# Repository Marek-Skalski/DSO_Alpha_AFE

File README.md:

# DSO_Alpha_AFE
This repository provides data related to DSO Alpha verision - AFE module

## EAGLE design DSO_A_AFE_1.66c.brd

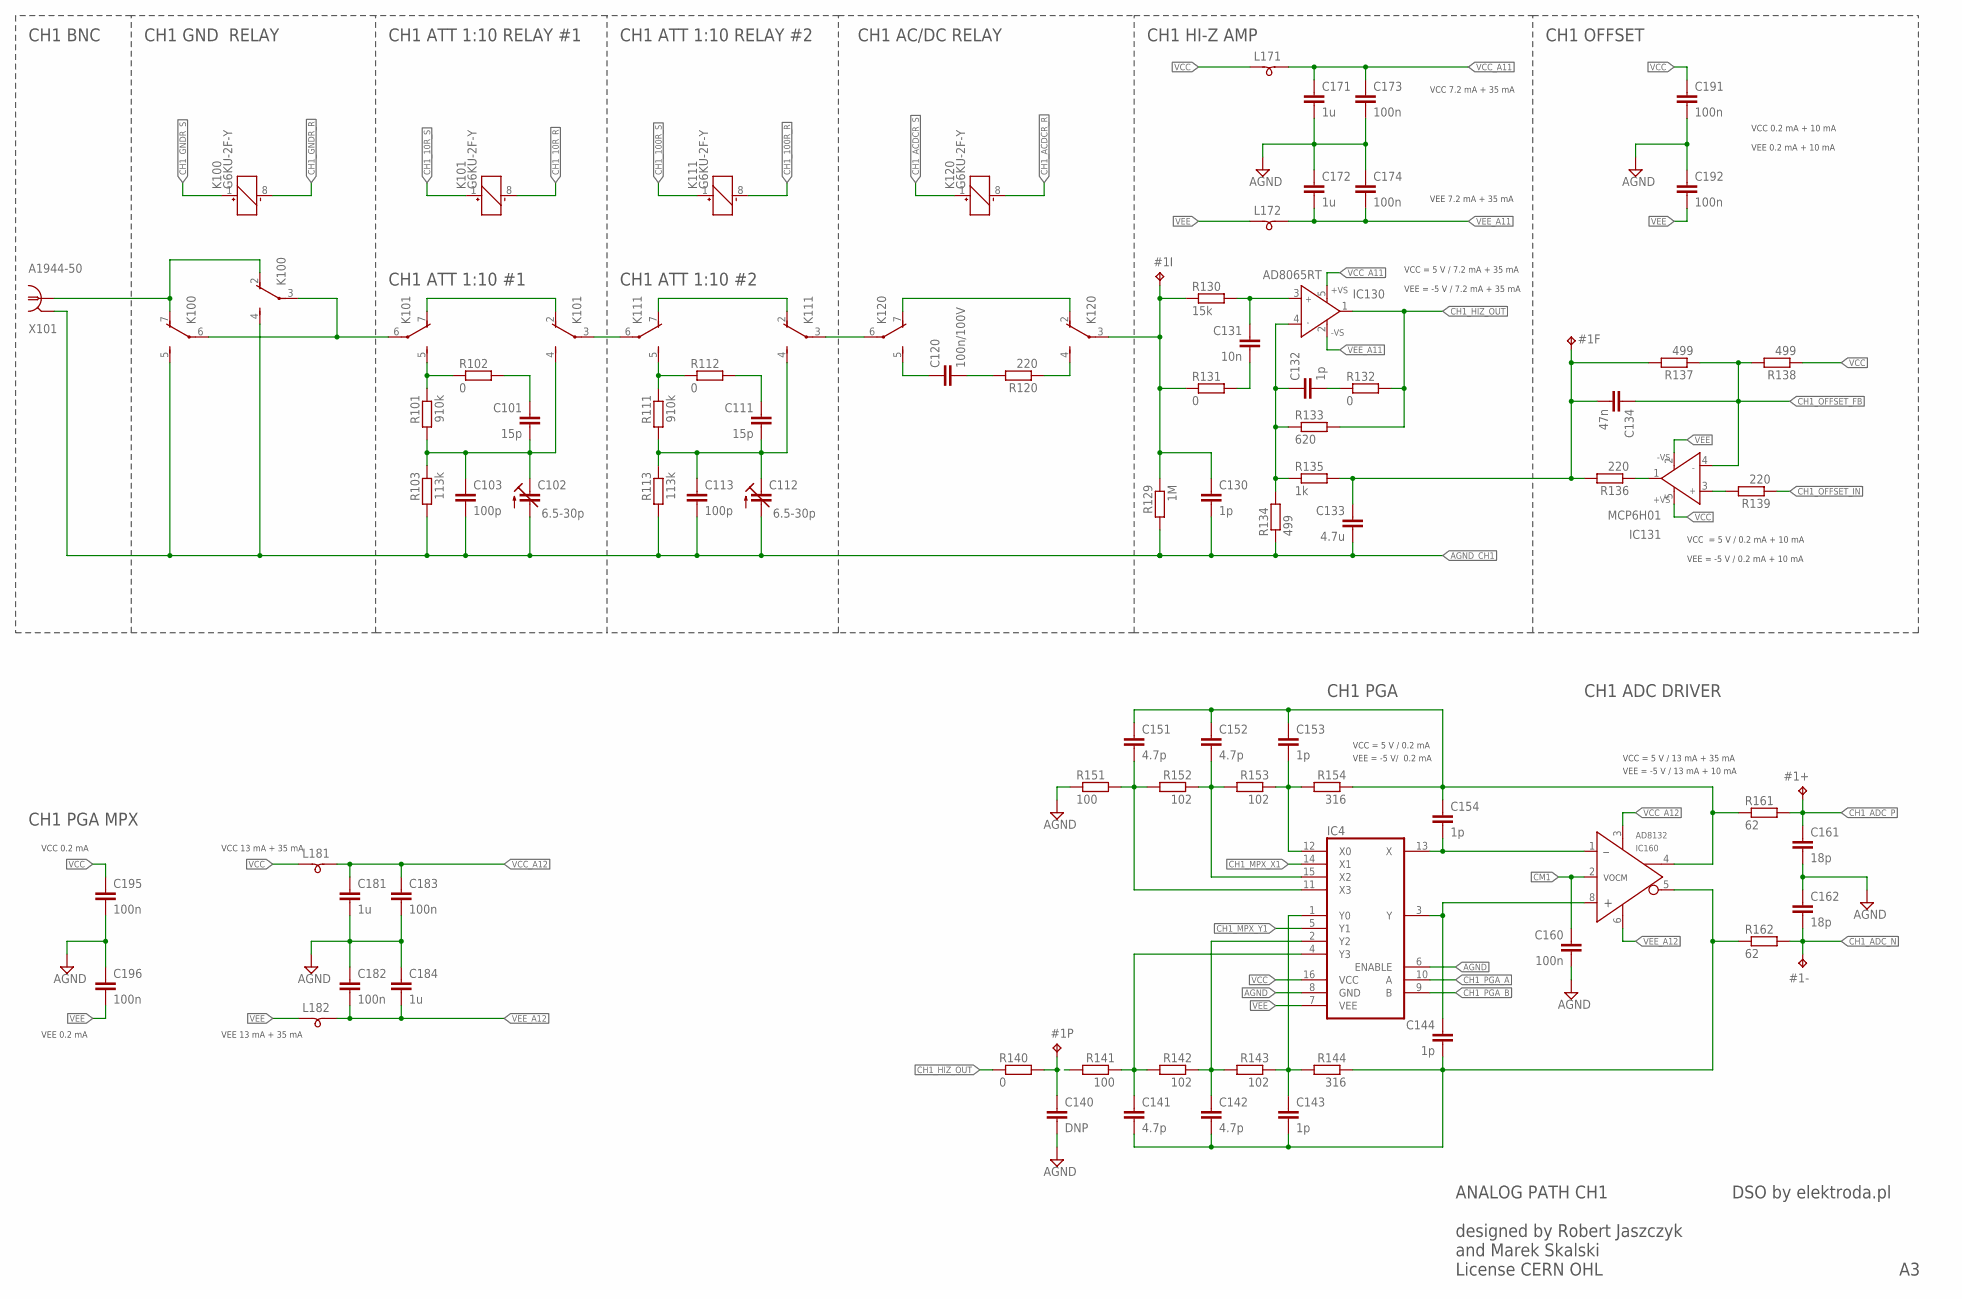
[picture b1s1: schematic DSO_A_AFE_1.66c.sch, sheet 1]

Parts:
#1+, #1-, #1F, #1I, #1P: TPB1,27; B1,27
C101, C111: 15p; C0603
C102, C112: 6.5-30p; CTRIMTZBX4
C103, C113: 100p; C0603
C120: 100n/100V; C1206
C130, C132, C143, C144, C153, C154: 1p; C0603
C131: 10n; C0603
C133: 4.7u; C0603
C134: 47n; C0603
C140: DNP; C0603
C141, C142, C151, C152: 4.7p; C0603
C160, C173, C174, C182, C183, C191, C192, C195, C196: 100n; C0603
C161, C162: 18p; C0603
C171, C172, C181, C184: 1u; C0603
IC4: DG4052EEQ; TSSOP16
IC130: AD8065RT; SOT23-5
IC131: MCP6H01; SOT23-5
IC160: AD8132; SO8
K100, K101, K111, K120: G6KU-2F-Y
L171, L172, L181, L182: SM-B0603; 0603
R101, R111: 910k; R0603
R102, R112, R131, R132, R140: 0; R0603
R103, R113: 113k; R0603
R120, R136, R139: 220; R0603
R129: 1M; R0603
R130: 15k; R0603
R133: 620; R0603
R134, R137, R138: 499; R0603
R135: 1k; R0603
R141, R151: 100; R0603
R142, R143, R152, R153: 102; R0603
R144, R154: 316; R0603
R161, R162: 62; R0603
X101: A1944-50; A1944

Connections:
AGND: C140.2, C160.2, C161.2, C162.1, C171.2, C172.1, C173.2, C174.1, C181.2, C182.1, C183.2, C184.1, C191.2, C192.1, C195.2, C196.1, IC4.6 (ENABLE), IC4.8 (GND), R151.1; also elsewhere on the board
AGND_CH1: C102.2 (A), C103.2, C112.2 (A), C113.2, C130.2, C133.2, K100.4 (S), K100.5 (S), R103.2, R113.2, R129.2, R134.1, X101.2, X101.3 (2), X101.4 (2), X101.5 (2); also elsewhere on the board
CH1_10R_R: K101.8 (-); also elsewhere on the board
CH1_10R_S: K101.1 (+); also elsewhere on the board
CH1_100R_R: K111.8 (-); also elsewhere on the board
CH1_100R_S: K111.1 (+); also elsewhere on the board
CH1_A1_C: C101.1, R102.2
CH1_A1_IN: K101.5 (S), R101.1, R102.1
CH1_A1_OUT: C101.2, C102.1 (E), C103.1, K101.4 (S), R101.2, R103.1
CH1_A2_C: C111.1, R112.2
CH1_A2_IN: K111.5 (S), R111.1, R112.1
CH1_A2_OUT: C111.2, C112.1 (E), C113.1, K111.4 (S), R111.2, R113.1
CH1_AC: C120.2, R120.2
CH1_ACDCR_R: K120.8 (-); also elsewhere on the board
CH1_ACDCR_S: K120.1 (+); also elsewhere on the board
CH1_ACI: C120.1, K120.5 (S)
CH1_ACO: K120.4 (S), R120.1
CH1_ADC_N: #1-.TP, C162.2, R162.2; also elsewhere on the board
CH1_ADC_P: #1+.TP, C161.1, R161.2; also elsewhere on the board
CH1_GNDR_R: K100.8 (-); also elsewhere on the board
CH1_GNDR_S: K100.1 (+); also elsewhere on the board
CH1_HIZ_IN: #1I.TP, C130.1, K120.3, R129.1, R130.1, R131.1
CH1_HIZ_IN+: C131.1, IC130.3 (IN+), R130.2
CH1_HIZ_IN-: C132.1, IC130.4 (IN-), R133.1, R134.2, R135.1
CH1_HIZ_OUT: IC130.1 (OUT), R132.2, R133.2, R140.1
CH1_IN: K100.2 (O), K100.7 (O), X101.1
CH1_IN01: K100.3, K100.6, K101.6
CH1_IN12: K101.3, K111.6
CH1_INA1: K101.2 (O), K101.7 (O)
CH1_INA2: K111.2 (O), K111.7 (O)
CH1_INA3: K120.2 (O), K120.7 (O)
CH1_INA23: K111.3, K120.6
CH1_IN_HIZ_C: C131.2, R131.2
CH1_MPX_X1: IC4.14 (X1)
CH1_MPX_Y1: IC4.5 (Y1)
CH1_OFFSET: #1F.TP, C133.1, C134.2, R135.2, R136.2, R137.2
CH1_OFFSET_FB: C134.1, IC131.4 (IN-), R137.1, R138.2; also elsewhere on the board
CH1_OFFSET_IN: R139.1; also elsewhere on the board
CH1_OFS_IN+: IC131.3 (IN+), R139.2
CH1_OFS_OUT_DIR: IC131.1 (OUT), R136.1
CH1_OUT_C: C132.2, R132.1
CH1_PGAN_DIR: C141.2, C142.2, C143.2, C144.2, IC160.5 (-OUT), R144.1, R162.1
CH1_PGA_A: IC4.10 (A); also elsewhere on the board
CH1_PGA_B: IC4.9 (B); also elsewhere on the board
CH1_PGA_IN: #1P.TP, C140.1, R140.2, R141.2
CH1_PGA_IN+: C144.1, IC4.3 (Y), IC160.8 (+IN)
CH1_PGA_IN-: C154.2, IC4.13 (X), IC160.1 (-IN)
CH1_PGA_N1: C143.1, IC4.1 (Y0), R143.1, R144.2
CH1_PGA_N2: C142.1, IC4.2 (Y2), R142.1, R143.2
CH1_PGA_N3: C141.1, IC4.4 (Y3), R141.1, R142.2
CH1_PGA_P1: C153.2, IC4.12 (X0), R153.1, R154.2
CH1_PGA_P2: C152.2, IC4.15 (X2), R152.1, R153.2
CH1_PGA_P3: C151.2, IC4.11 (X3), R151.2, R152.2
CH1_PGA_P_DIR: C151.1, C152.1, C153.1, C154.1, IC160.4 (+OUT), R154.1, R161.1
CM1: C160.1, IC160.2 (VOCM); also elsewhere on the board
VCC: C191.1, C195.1, IC4.16 (VCC), IC131.5 (+VS), L171.1, L181.1, R138.1; also elsewhere on the board
VCC_A11: C171.1, C173.1, IC130.5 (+VS), L171.2
VCC_A12: C181.1, C183.1, IC160.3 (V+), L181.2
VEE: C192.2, C196.2, IC4.7 (VEE), IC131.2 (-VS), L172.1, L182.1; also elsewhere on the board
VEE_A11: C172.2, C174.2, IC130.2 (-VS), L172.2
VEE_A12: C182.2, C184.2, IC160.6 (V-), L182.2

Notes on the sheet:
ANALOG PATH CH1 designed by Robert Jaszczyk and Marek Skalski License CERN OHL
DSO by elektroda.pl
CH1 BNC
CH1 ATT 1:10 #1
CH1 ATT 1:10 #2
CH1 HI-Z AMP
CH1 ADC DRIVER
CH1 OFFSET
CH1 ATT 1:10 RELAY #1
CH1 ATT 1:10 RELAY #2
CH1 AC/DC RELAY
VEE = -5 V / 13 mA + 10 mA
VCC = 5 V / 13 mA + 35 mA
VEE = -5 V / 0.2 mA + 10 mA
VCC = 5 V / 0.2 mA + 10 mA
VCC = 5 V / 0.2 mA
VEE = -5 V/ 0.2 mA
CH1 GND RELAY
VCC = 5 V / 7.2 mA + 35 mA
VEE = -5 V / 7.2 mA + 35 mA
VCC 0.2 mA + 10 mA
VEE 0.2 mA + 10 mA
CH1 PGA MPX
VCC 0.2 mA
VEE 0.2 mA
VCC 13 mA + 35 mA
VEE 13 mA + 35 mA
CH1 PGA
VCC 7.2 mA + 35 mA
VEE 7.2 mA + 35 mA

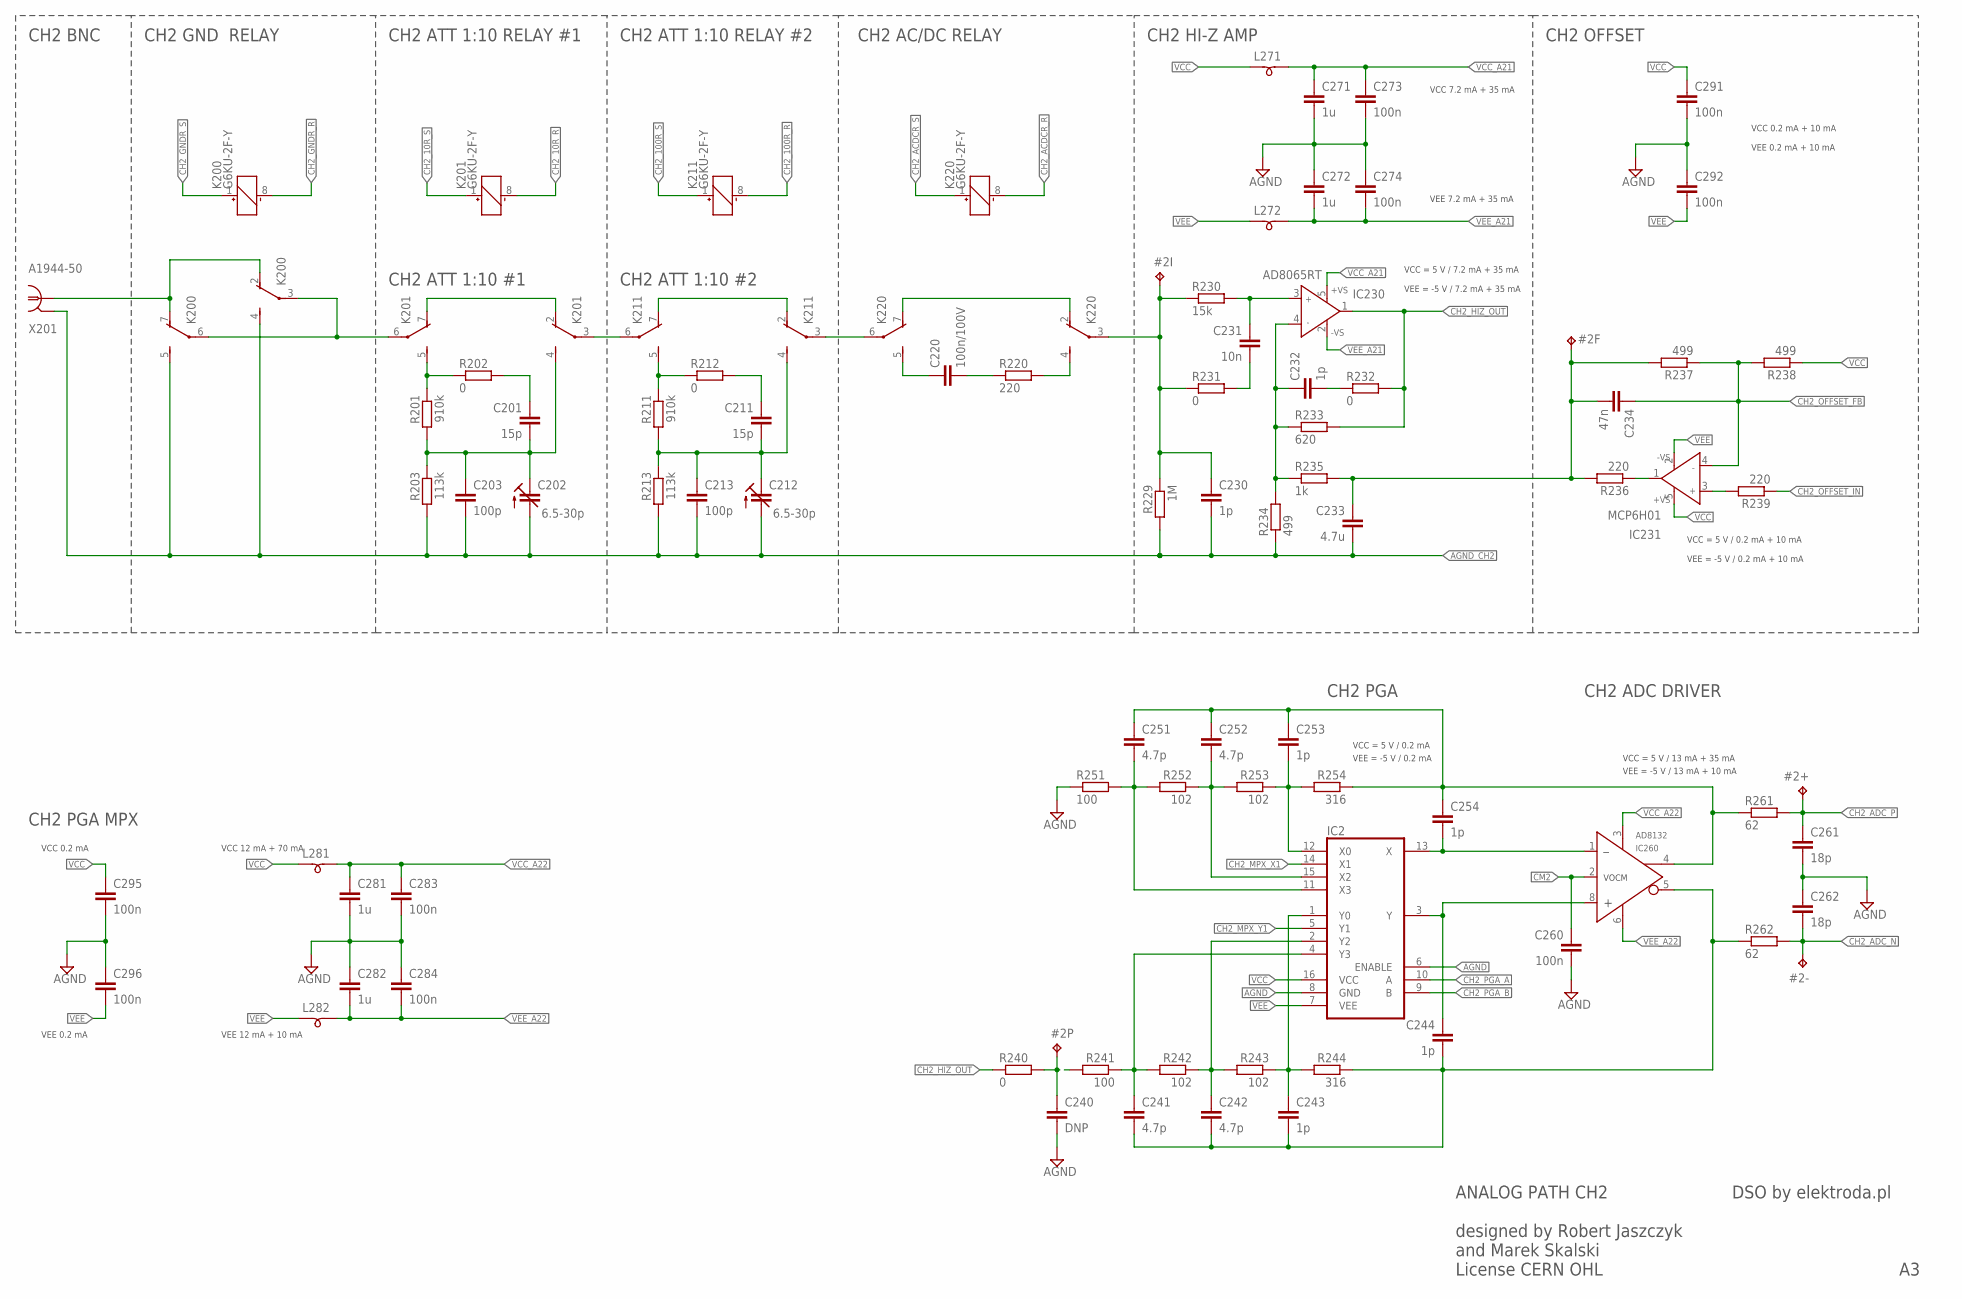
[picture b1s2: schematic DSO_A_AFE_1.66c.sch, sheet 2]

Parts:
#2+, #2-, #2F, #2I, #2P: TPB1,27; B1,27
C201, C211: 15p; C0603
C202, C212: 6.5-30p; CTRIMTZBX4
C203, C213: 100p; C0603
C220: 100n/100V; C1206
C230, C232, C243, C244, C253, C254: 1p; C0603
C231: 10n; C0603
C233: 4.7u; C0603
C234: 47n; C0603
C240: DNP; C0603
C241, C242, C251, C252: 4.7p; C0603
C260, C273, C274, C283, C284, C291, C292, C295, C296: 100n; C0603
C261, C262: 18p; C0603
C271, C272, C281, C282: 1u; C0603
IC2: DG4052EEQ; TSSOP16
IC230: AD8065RT; SOT23-5
IC231: MCP6H01; SOT23-5
IC260: AD8132; SO8
K200, K201, K211, K220: G6KU-2F-Y
L271, L272, L281, L282: SM-B0603; 0603
R201, R211: 910k; R0603
R202, R212, R231, R232, R240: 0; R0603
R203, R213: 113k; R0603
R220, R236, R239: 220; R0603
R229: 1M; R0603
R230: 15k; R0603
R233: 620; R0603
R234, R237, R238: 499; R0603
R235: 1k; R0603
R241, R251: 100; R0603
R242, R243, R252, R253: 102; R0603
R244, R254: 316; R0603
R261, R262: 62; R0603
X201: A1944-50; A1944

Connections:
AGND: C240.2, C260.2, C261.2, C262.1, C271.2, C272.1, C273.2, C274.1, C281.2, C282.1, C283.2, C284.1, C291.2, C292.1, C295.2, C296.1, IC2.6 (ENABLE), IC2.8 (GND), R251.1; also elsewhere on the board
AGND_CH2: C202.2 (A), C203.2, C212.2 (A), C213.2, C230.2, C233.2, K200.4 (S), K200.5 (S), R203.2, R213.2, R229.2, R234.1, X201.2, X201.3 (2), X201.4 (2), X201.5 (2); also elsewhere on the board
CH1_OFS_OUT_DIR1: IC231.1 (OUT), R236.1
CH2_10R_R: K201.8 (-); also elsewhere on the board
CH2_10R_S: K201.1 (+); also elsewhere on the board
CH2_100R_R: K211.8 (-); also elsewhere on the board
CH2_100R_S: K211.1 (+); also elsewhere on the board
CH2_A1_C: C201.1, R202.2
CH2_A1_IN: K201.5 (S), R201.1, R202.1
CH2_A1_OUT: C201.2, C202.1 (E), C203.1, K201.4 (S), R201.2, R203.1
CH2_A2_C: C211.1, R212.2
CH2_A2_IN: K211.5 (S), R211.1, R212.1
CH2_A2_OUT: C211.2, C212.1 (E), C213.1, K211.4 (S), R211.2, R213.1
CH2_AC: C220.2, R220.1
CH2_ACDCR_R: K220.8 (-); also elsewhere on the board
CH2_ACDCR_S: K220.1 (+); also elsewhere on the board
CH2_ACI: C220.1, K220.5 (S)
CH2_ACO: K220.4 (S), R220.2
CH2_ADC_N: #2-.TP, C262.2, R262.2; also elsewhere on the board
CH2_ADC_P: #2+.TP, C261.1, R261.2; also elsewhere on the board
CH2_GNDR_R: K200.8 (-); also elsewhere on the board
CH2_GNDR_S: K200.1 (+); also elsewhere on the board
CH2_HIZ_IN: #2I.TP, C230.1, K220.3, R229.1, R230.1, R231.1
CH2_HIZ_IN+: C231.1, IC230.3 (IN+), R230.2
CH2_HIZ_IN-: C232.1, IC230.4 (IN-), R233.1, R234.2, R235.1
CH2_HIZ_OUT: IC230.1 (OUT), R232.2, R233.2, R240.1
CH2_IN: K200.2 (O), K200.7 (O), X201.1
CH2_IN01: K200.3, K200.6, K201.6
CH2_IN12: K201.3, K211.6
CH2_INA1: K201.2 (O), K201.7 (O)
CH2_INA2: K211.2 (O), K211.7 (O)
CH2_INA3: K220.2 (O), K220.7 (O)
CH2_INA23: K211.3, K220.6
CH2_IN_HIZ_C: C231.2, R231.2
CH2_MPX_X1: IC2.14 (X1)
CH2_MPX_Y1: IC2.5 (Y1)
CH2_OFFSET: #2F.TP, C233.1, C234.2, R235.2, R236.2, R237.2
CH2_OFFSET_FB: C234.1, IC231.4 (IN-), R237.1, R238.2; also elsewhere on the board
CH2_OFFSET_IN: R239.1; also elsewhere on the board
CH2_OFS_IN+: IC231.3 (IN+), R239.2
CH2_OUT_C: C232.2, R232.1
CH2_PGAN_DIR: C241.2, C242.2, C243.2, C244.2, IC260.5 (-OUT), R244.1, R262.1
CH2_PGA_A: IC2.10 (A); also elsewhere on the board
CH2_PGA_B: IC2.9 (B); also elsewhere on the board
CH2_PGA_IN1: #2P.TP, C240.1, R240.2, R241.2
CH2_PGA_IN+: C244.1, IC2.3 (Y), IC260.8 (+IN)
CH2_PGA_IN-: C254.2, IC2.13 (X), IC260.1 (-IN)
CH2_PGA_N1: C243.1, IC2.1 (Y0), R243.1, R244.2
CH2_PGA_N2: C242.1, IC2.2 (Y2), R242.1, R243.2
CH2_PGA_N5: C241.1, IC2.4 (Y3), R241.1, R242.2
CH2_PGA_P1: C253.2, IC2.12 (X0), R253.1, R254.2
CH2_PGA_P2: C252.2, IC2.15 (X2), R252.1, R253.2
CH2_PGA_P5: C251.2, IC2.11 (X3), R251.2, R252.2
CH2_PGA_P_DIR: C251.1, C252.1, C253.1, C254.1, IC260.4 (+OUT), R254.1, R261.1
CM2: C260.1, IC260.2 (VOCM); also elsewhere on the board
VCC: C291.1, C295.1, IC2.16 (VCC), IC231.5 (+VS), L271.1, L281.1, R238.1; also elsewhere on the board
VCC_A21: C271.1, C273.1, IC230.5 (+VS), L271.2
VCC_A22: C281.1, C283.1, IC260.3 (V+), L281.2
VEE: C292.2, C296.2, IC2.7 (VEE), IC231.2 (-VS), L272.1, L282.1; also elsewhere on the board
VEE_A21: C272.2, C274.2, IC230.2 (-VS), L272.2
VEE_A22: C282.2, C284.2, IC260.6 (V-), L282.2

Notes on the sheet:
ANALOG PATH CH2 designed by Robert Jaszczyk and Marek Skalski License CERN OHL
DSO by elektroda.pl
CH2 BNC
CH2 ATT 1:10 #1
CH2 ATT 1:10 #2
CH2 HI-Z AMP
CH2 ADC DRIVER
CH2 OFFSET
CH2 ATT 1:10 RELAY #1
CH2 ATT 1:10 RELAY #2
CH2 AC/DC RELAY
VEE = -5 V / 13 mA + 10 mA
VCC = 5 V / 13 mA + 35 mA
VEE = -5 V / 0.2 mA + 10 mA
VCC = 5 V / 0.2 mA + 10 mA
VCC = 5 V / 0.2 mA
VEE = -5 V / 0.2 mA
CH2 GND RELAY
VCC 7.2 mA + 35 mA
VEE 7.2 mA + 35 mA
VCC 0.2 mA + 10 mA
VEE 0.2 mA + 10 mA
CH2 PGA MPX
VCC 0.2 mA
VEE 0.2 mA
VCC 12 mA + 70 mA
VEE 12 mA + 10 mA
CH2 PGA
VCC = 5 V / 7.2 mA + 35 mA
VEE = -5 V / 7.2 mA + 35 mA

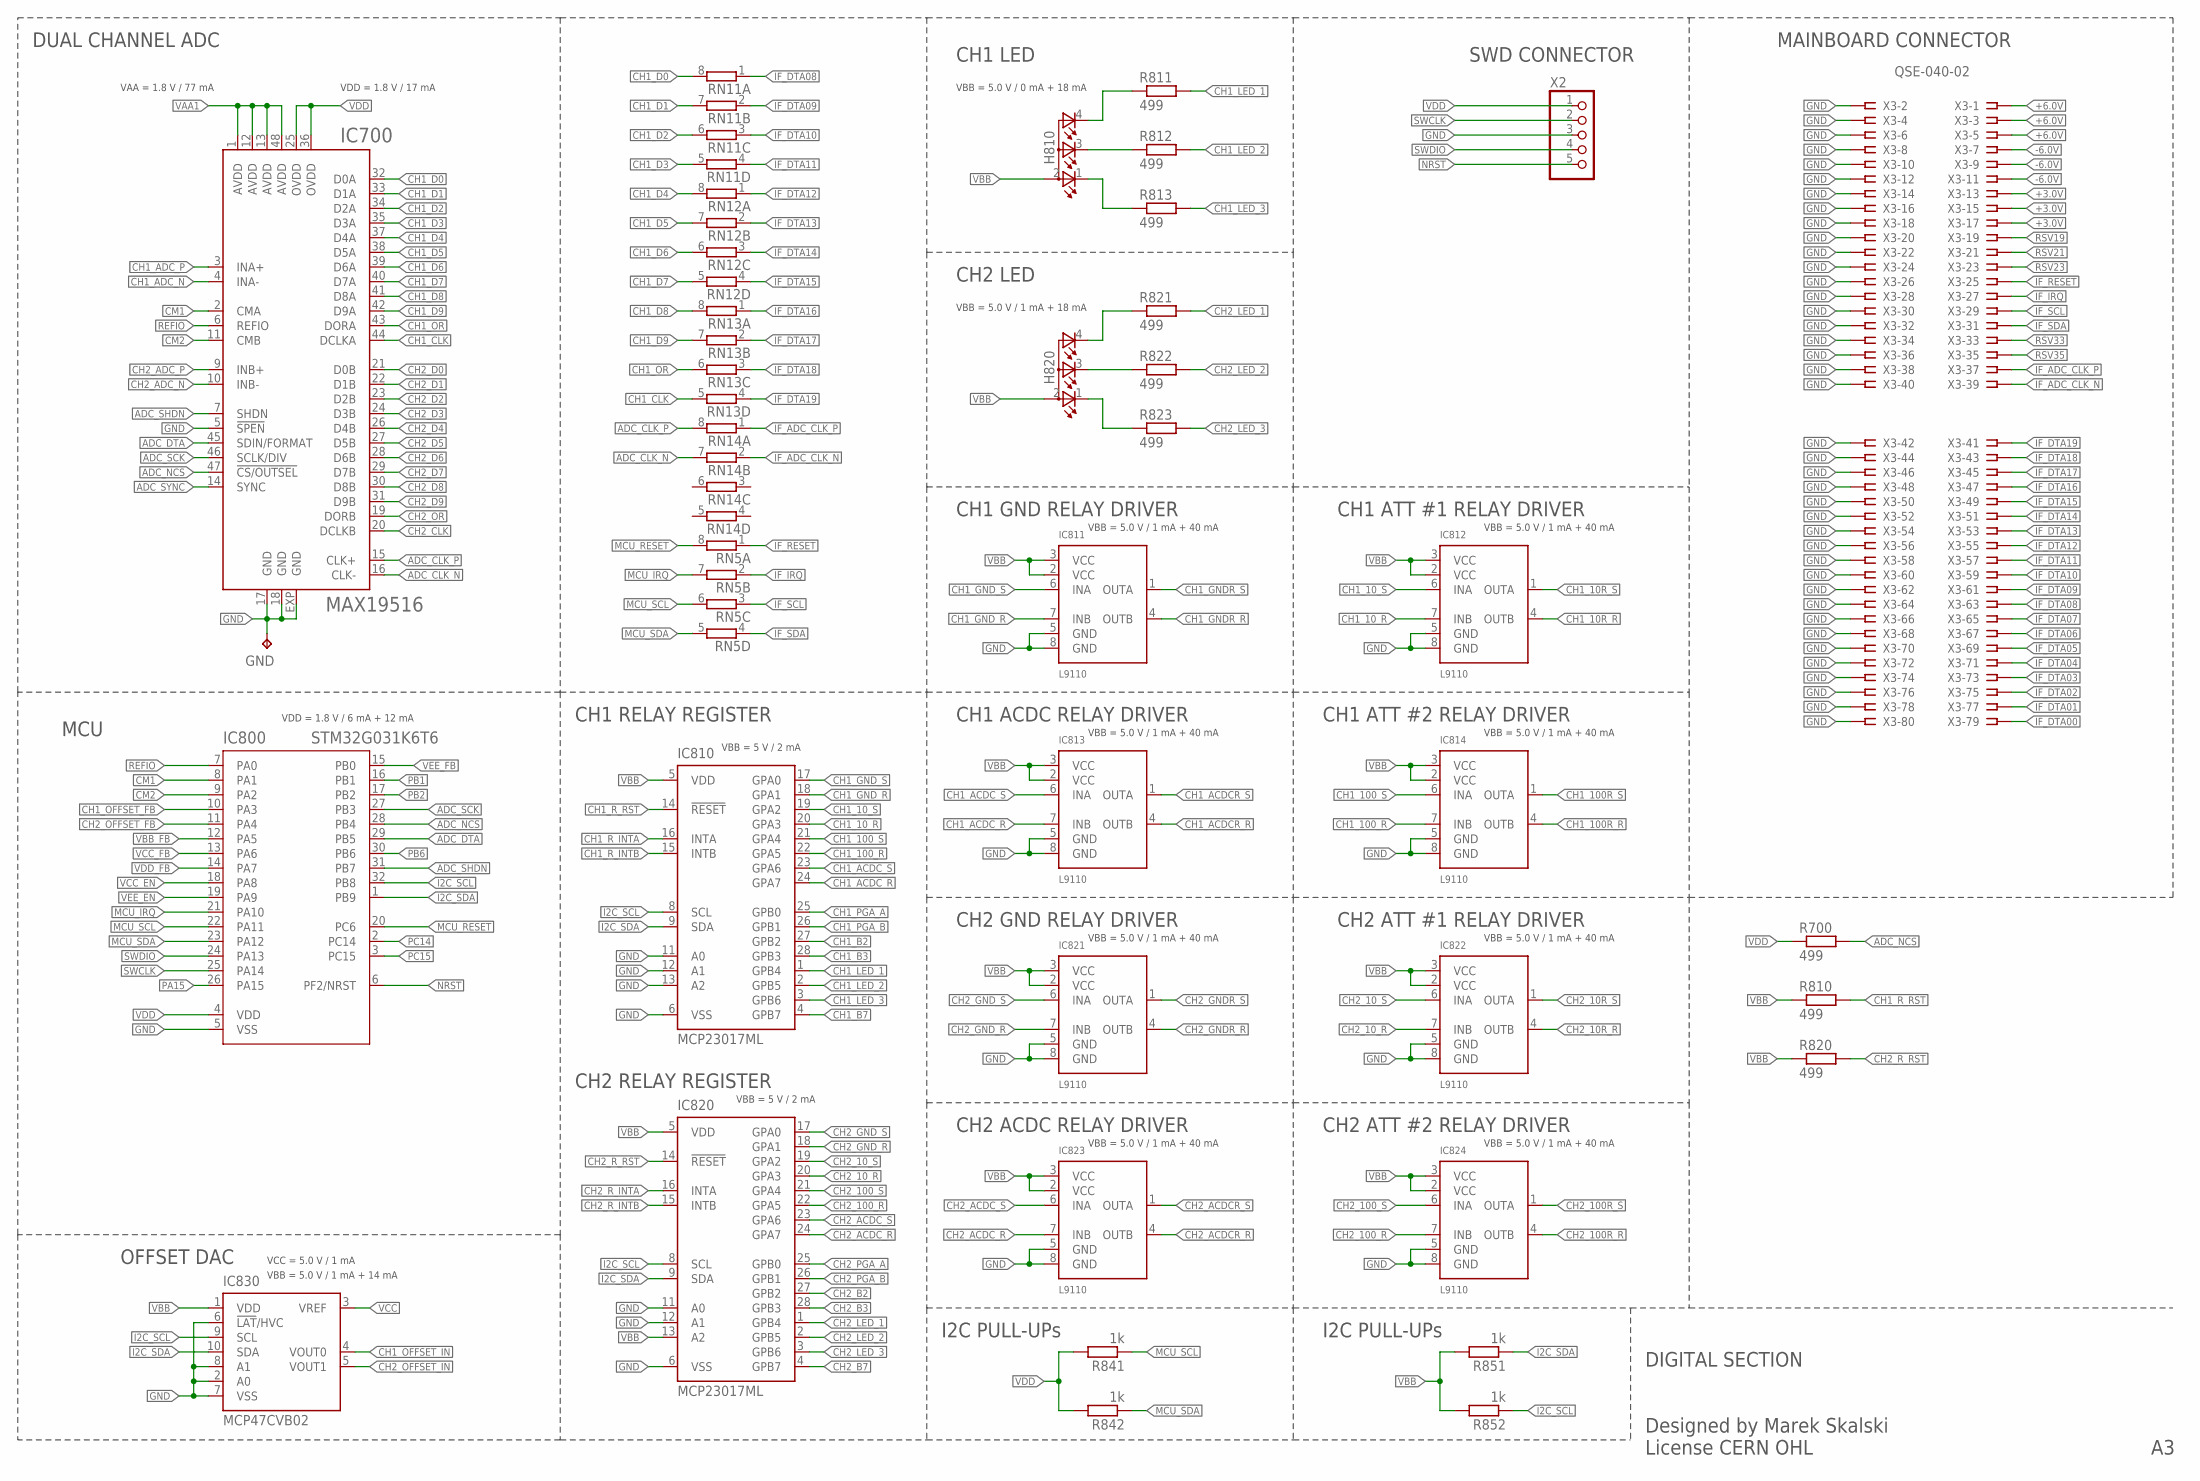
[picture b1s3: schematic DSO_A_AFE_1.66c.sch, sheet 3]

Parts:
GND: TPB1,27; B1,27
H810, H820: CREE_PLCC4_RGB; PLCC4_CREE
IC700: MAX19516; TQFN48-EP
IC800: STM32G031K6T6; LQFP32_7X7
IC810, IC820: MCP23017ML; QFN28-ML_6X6MM
IC811, IC812, IC813, IC814, IC821, IC822, IC823, IC824: L9110; SO08
IC830: MCP47CVB02; MSOP10
R700, R810, R811, R812, R813, R820, R821, R822, R823: 499; R0603
R841, R842, R851, R852: 1k; R0603
RN5, RN11, RN12, RN13, RN14: 4R-N0603-ARC; 0603-ARC
X2: PINHD-1X5/90; 1X05/90
X3: QSE-040-02

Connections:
+3.0V: X3.13, X3.15, X3.17; also elsewhere on the board
+6.0V: X3.1, X3.3, X3.5; also elsewhere on the board
-6.0V: X3.7, X3.9, X3.11; also elsewhere on the board
ADC_CLK_N: IC700.16 (CLK-), RN14.7 (2)
ADC_CLK_P: IC700.15 (CLK+), RN14.8 (2)
ADC_DTA: IC700.45 (SDIN/FORMAT), IC800.29 (PB5)
ADC_NCS: IC700.47 (!CS/OUTSEL), IC800.28 (PB4), R700.2
ADC_SCK: IC700.46 (SCLK/DIV), IC800.27 (PB3)
ADC_SHDN: IC700.7 (SHDN), IC800.31 (PB7)
ADC_SYNC: IC700.14 (SYNC)
CH1_10R_R: IC812.4 (OUTB); also elsewhere on the board
CH1_10R_S: IC812.1 (OUTA); also elsewhere on the board
CH1_10_R: IC810.20 (GPA3), IC812.7 (INB)
CH1_10_S: IC810.19 (GPA2), IC812.6 (INA)
CH1_100R_R: IC814.4 (OUTB); also elsewhere on the board
CH1_100R_S: IC814.1 (OUTA); also elsewhere on the board
CH1_100_R: IC810.22 (GPA5), IC814.7 (INB)
CH1_100_S: IC810.21 (GPA4), IC814.6 (INA)
CH1_ACDCR_R: IC813.4 (OUTB); also elsewhere on the board
CH1_ACDCR_S: IC813.1 (OUTA); also elsewhere on the board
CH1_ACDC_R: IC810.24 (GPA7), IC813.7 (INB)
CH1_ACDC_S: IC810.23 (GPA6), IC813.6 (INA)
CH1_ADC_N: IC700.4 (INA-); also elsewhere on the board
CH1_ADC_P: IC700.3 (INA+); also elsewhere on the board
CH1_B2: IC810.27 (GPB2); also elsewhere on the board
CH1_B3: IC810.28 (GPB3); also elsewhere on the board
CH1_B7: IC810.4 (GPB7); also elsewhere on the board
CH1_CLK: IC700.44 (DCLKA), RN13.5 (2)
CH1_D0: IC700.32 (D0A), RN11.8 (2)
CH1_D1: IC700.33 (D1A), RN11.7 (2)
CH1_D2: IC700.34 (D2A), RN11.6 (2)
CH1_D3: IC700.35 (D3A), RN11.5 (2)
CH1_D4: IC700.37 (D4A), RN12.8 (2)
CH1_D5: IC700.38 (D5A), RN12.7 (2)
CH1_D6: IC700.39 (D6A), RN12.6 (2)
CH1_D7: IC700.40 (D7A), RN12.5 (2)
CH1_D8: IC700.41 (D8A), RN13.8 (2)
CH1_D9: IC700.42 (D9A), RN13.7 (2)
CH1_GNDR_R: IC811.4 (OUTB); also elsewhere on the board
CH1_GNDR_S: IC811.1 (OUTA); also elsewhere on the board
CH1_GND_R: IC810.18 (GPA1), IC811.7 (INB)
CH1_GND_S: IC810.17 (GPA0), IC811.6 (INA)
CH1_LED1: H810.4 (CGREEN), R811.1
CH1_LED2: H810.3 (CBLUE), R812.1
CH1_LED3: H810.1 (CRED), R813.1
CH1_LED_1: IC810.1 (GPB4), R811.2
CH1_LED_2: IC810.2 (GPB5), R812.2
CH1_LED_3: IC810.3 (GPB6), R813.2
CH1_OFFSET_FB: IC800.10 (PA3); also elsewhere on the board
CH1_OFFSET_IN: IC830.4 (VOUT0); also elsewhere on the board
CH1_OR: IC700.43 (DORA), RN13.6 (2)
CH1_PGA_A: IC810.25 (GPB0); also elsewhere on the board
CH1_PGA_B: IC810.26 (GPB1); also elsewhere on the board
CH1_R_INTA: IC810.16 (INTA)
CH1_R_INTB: IC810.15 (INTB)
CH1_R_RST: IC810.14 (!RESET), R810.2
CH2_10R_R: IC822.4 (OUTB); also elsewhere on the board
CH2_10R_S: IC822.1 (OUTA); also elsewhere on the board
CH2_10_R: IC820.20 (GPA3), IC822.7 (INB)
CH2_10_S: IC820.19 (GPA2), IC822.6 (INA)
CH2_100R_R: IC824.4 (OUTB); also elsewhere on the board
CH2_100R_S: IC824.1 (OUTA); also elsewhere on the board
CH2_100_R: IC820.22 (GPA5), IC824.7 (INB)
CH2_100_S: IC820.21 (GPA4), IC824.6 (INA)
CH2_ACDCR_R: IC823.4 (OUTB); also elsewhere on the board
CH2_ACDCR_S: IC823.1 (OUTA); also elsewhere on the board
CH2_ACDC_R: IC820.24 (GPA7), IC823.7 (INB)
CH2_ACDC_S: IC820.23 (GPA6), IC823.6 (INA)
CH2_ADC_N: IC700.10 (INB-); also elsewhere on the board
CH2_ADC_P: IC700.9 (INB+); also elsewhere on the board
CH2_B2: IC820.27 (GPB2); also elsewhere on the board
CH2_B3: IC820.28 (GPB3); also elsewhere on the board
CH2_B7: IC820.4 (GPB7); also elsewhere on the board
CH2_CLK: IC700.20 (DCLKB)
CH2_D0: IC700.21 (D0B)
CH2_D1: IC700.22 (D1B)
CH2_D2: IC700.23 (D2B)
CH2_D3: IC700.24 (D3B)
CH2_D4: IC700.26 (D4B)
CH2_D5: IC700.27 (D5B)
CH2_D6: IC700.28 (D6B)
CH2_D7: IC700.29 (D7B)
CH2_D8: IC700.30 (D8B)
CH2_D9: IC700.31 (D9B)
CH2_GNDR_R: IC821.4 (OUTB); also elsewhere on the board
CH2_GNDR_S: IC821.1 (OUTA); also elsewhere on the board
CH2_GND_R: IC820.18 (GPA1), IC821.7 (INB)
CH2_GND_S: IC820.17 (GPA0), IC821.6 (INA)
CH2_LED1: H820.4 (CGREEN), R821.1
CH2_LED2: H820.3 (CBLUE), R822.1
CH2_LED3: H820.1 (CRED), R823.1
CH2_LED_1: IC820.1 (GPB4), R821.2
CH2_LED_2: IC820.2 (GPB5), R822.2
CH2_LED_3: IC820.3 (GPB6), R823.2
CH2_OFFSET_FB: IC800.11 (PA4); also elsewhere on the board
CH2_OFFSET_IN: IC830.5 (VOUT1); also elsewhere on the board
CH2_OR: IC700.19 (DORB)
CH2_PGA_A: IC820.25 (GPB0); also elsewhere on the board
CH2_PGA_B: IC820.26 (GPB1); also elsewhere on the board
CH2_R_INTA: IC820.16 (INTA)
CH2_R_INTB: IC820.15 (INTB)
CH2_R_RST: IC820.14 (!RESET), R820.2
CM1: IC700.2 (CMA), IC800.8 (PA1); also elsewhere on the board
CM2: IC700.11 (CMB), IC800.9 (PA2); also elsewhere on the board
GND: GND.TP, IC700.5 (!SPEN), IC700.17 (GND), IC700.18 (GND), IC700.EXP (GND), IC800.5 (VSS), IC810.6 (VSS), IC810.11 (A0), IC810.12 (A1), IC810.13 (A2), IC811.5 (GND), IC811.8 (GND), IC812.5 (GND), IC812.8 (GND), IC813.5 (GND), IC813.8 (GND), IC814.5 (GND), IC814.8 (GND), IC820.6 (VSS), IC820.11 (A0), IC820.12 (A1), IC821.5 (GND), IC821.8 (GND), IC822.5 (GND), IC822.8 (GND), IC823.5 (GND), IC823.8 (GND), IC824.5 (GND), IC824.8 (GND), IC830.2 (A0), IC830.6 (!LAT!/HVC), IC830.7 (VSS), IC830.8 (A1), X2.3, X3.2, X3.4, X3.6, X3.8, X3.10, X3.12, X3.14, X3.16, X3.18, X3.20, X3.22, X3.24, X3.26, X3.28, X3.30, X3.32, X3.34, X3.36, X3.38, X3.40, X3.42, X3.44, X3.46, X3.48, X3.50, X3.52, X3.54, X3.56, X3.58, X3.60, X3.62, X3.64, X3.66, X3.68, X3.70, X3.72, X3.74, X3.76, X3.78, X3.80; also elsewhere on the board
I2C_SCL: IC800.32 (PB8), IC810.8 (SCL), IC820.8 (SCL), IC830.9 (SCL), R852.1
I2C_SDA: IC800.1 (PB9), IC810.9 (SDA), IC820.9 (SDA), IC830.10 (SDA), R851.1
IF_ADC_CLK_N: RN14.2 (1), X3.39
IF_ADC_CLK_P: RN14.1, X3.37
IF_DTA00: X3.79
IF_DTA01: X3.77
IF_DTA02: X3.75
IF_DTA03: X3.73
IF_DTA04: X3.71
IF_DTA05: X3.69
IF_DTA06: X3.67
IF_DTA07: X3.65
IF_DTA08: RN11.1, X3.63
IF_DTA09: RN11.2 (1), X3.61
IF_DTA10: RN11.3 (1), X3.59
IF_DTA11: RN11.4 (1), X3.57
IF_DTA12: RN12.1, X3.55
IF_DTA13: RN12.2 (1), X3.53
IF_DTA14: RN12.3 (1), X3.51
IF_DTA15: RN12.4 (1), X3.49
IF_DTA16: RN13.1, X3.47
IF_DTA17: RN13.2 (1), X3.45
IF_DTA18: RN13.3 (1), X3.43
IF_DTA19: RN13.4 (1), X3.41
IF_IRQ: RN5.2 (1), X3.27
IF_RESET: RN5.1, X3.25
IF_SCL: RN5.3 (1), X3.29
IF_SDA: RN5.4 (1), X3.31
MCU_IRQ: IC800.21 (PA10), RN5.7 (2)
MCU_RESET: IC800.20 (PC6), RN5.8 (2)
MCU_SCL: IC800.22 (PA11), R841.1, RN5.6 (2)
MCU_SDA: IC800.23 (PA12), R842.1, RN5.5 (2)
NRST: IC800.6 (PF2/NRST), X2.5
PA15: IC800.26 (PA15); also elsewhere on the board
PB1: IC800.16 (PB1); also elsewhere on the board
PB2: IC800.17 (PB2); also elsewhere on the board
PB6: IC800.30 (PB6)
PC14: IC800.2 (PC14)
PC15: IC800.3 (PC15)
REFIO: IC700.6 (REFIO), IC800.7 (PA0); also elsewhere on the board
RSV19: X3.19
RSV21: X3.21
RSV23: X3.23
RSV33: X3.33
RSV35: X3.35
SWCLK: IC800.25 (PA14), X2.2
SWDIO: IC800.24 (PA13), X2.4
VAA1: IC700.1 (AVDD), IC700.12 (AVDD), IC700.13 (AVDD), IC700.48 (AVDD); also elsewhere on the board
VBB: H810.2 (A3), H820.2 (A3), IC810.5 (VDD), IC811.2 (VCC), IC811.3 (VCC), IC812.2 (VCC), IC812.3 (VCC), IC813.2 (VCC), IC813.3 (VCC), IC814.2 (VCC), IC814.3 (VCC), IC820.5 (VDD), IC820.13 (A2), IC821.2 (VCC), IC821.3 (VCC), IC822.2 (VCC), IC822.3 (VCC), IC823.2 (VCC), IC823.3 (VCC), IC824.2 (VCC), IC824.3 (VCC), IC830.1 (VDD), R810.1, R820.1, R851.2, R852.2; also elsewhere on the board
VBB_FB: IC800.12 (PA5); also elsewhere on the board
VCC: IC830.3 (VREF); also elsewhere on the board
VCC_EN: IC800.18 (PA8); also elsewhere on the board
VCC_FB: IC800.13 (PA6); also elsewhere on the board
VDD: IC700.25 (OVDD), IC700.36 (OVDD), IC800.4 (VDD), R700.1, R841.2, R842.2, X2.1; also elsewhere on the board
VDD_FB: IC800.14 (PA7); also elsewhere on the board
VEE_EN: IC800.19 (PA9); also elsewhere on the board
VEE_FB: IC800.15 (PB0); also elsewhere on the board

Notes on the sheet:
DIGITAL SECTION Designed by Marek Skalski License CERN OHL
DUAL CHANNEL ADC
MAINBOARD CONNECTOR
OFFSET DAC
VDD = 1.8 V / 17 mA
VAA = 1.8 V / 77 mA
MCU
CH1 RELAY REGISTER
CH1 ATT #1 RELAY DRIVER
CH1 ATT #2 RELAY DRIVER
CH2 ATT #1 RELAY DRIVER
CH2 ATT #2 RELAY DRIVER
CH1 LED
CH2 LED
I2C PULL-UPs
SWD CONNECTOR
CH1 GND RELAY DRIVER
CH1 ACDC RELAY DRIVER
CH2 GND RELAY DRIVER
CH2 ACDC RELAY DRIVER
VDD = 1.8 V / 6 mA + 12 mA
VBB = 5 V / 2 mA
CH2 RELAY REGISTER
VCC = 5.0 V / 1 mA
VBB = 5.0 V / 1 mA + 14 mA
VBB = 5.0 V / 1 mA + 40 mA
VBB = 5.0 V / 0 mA + 18 mA
VBB = 5.0 V / 1 mA + 18 mA
